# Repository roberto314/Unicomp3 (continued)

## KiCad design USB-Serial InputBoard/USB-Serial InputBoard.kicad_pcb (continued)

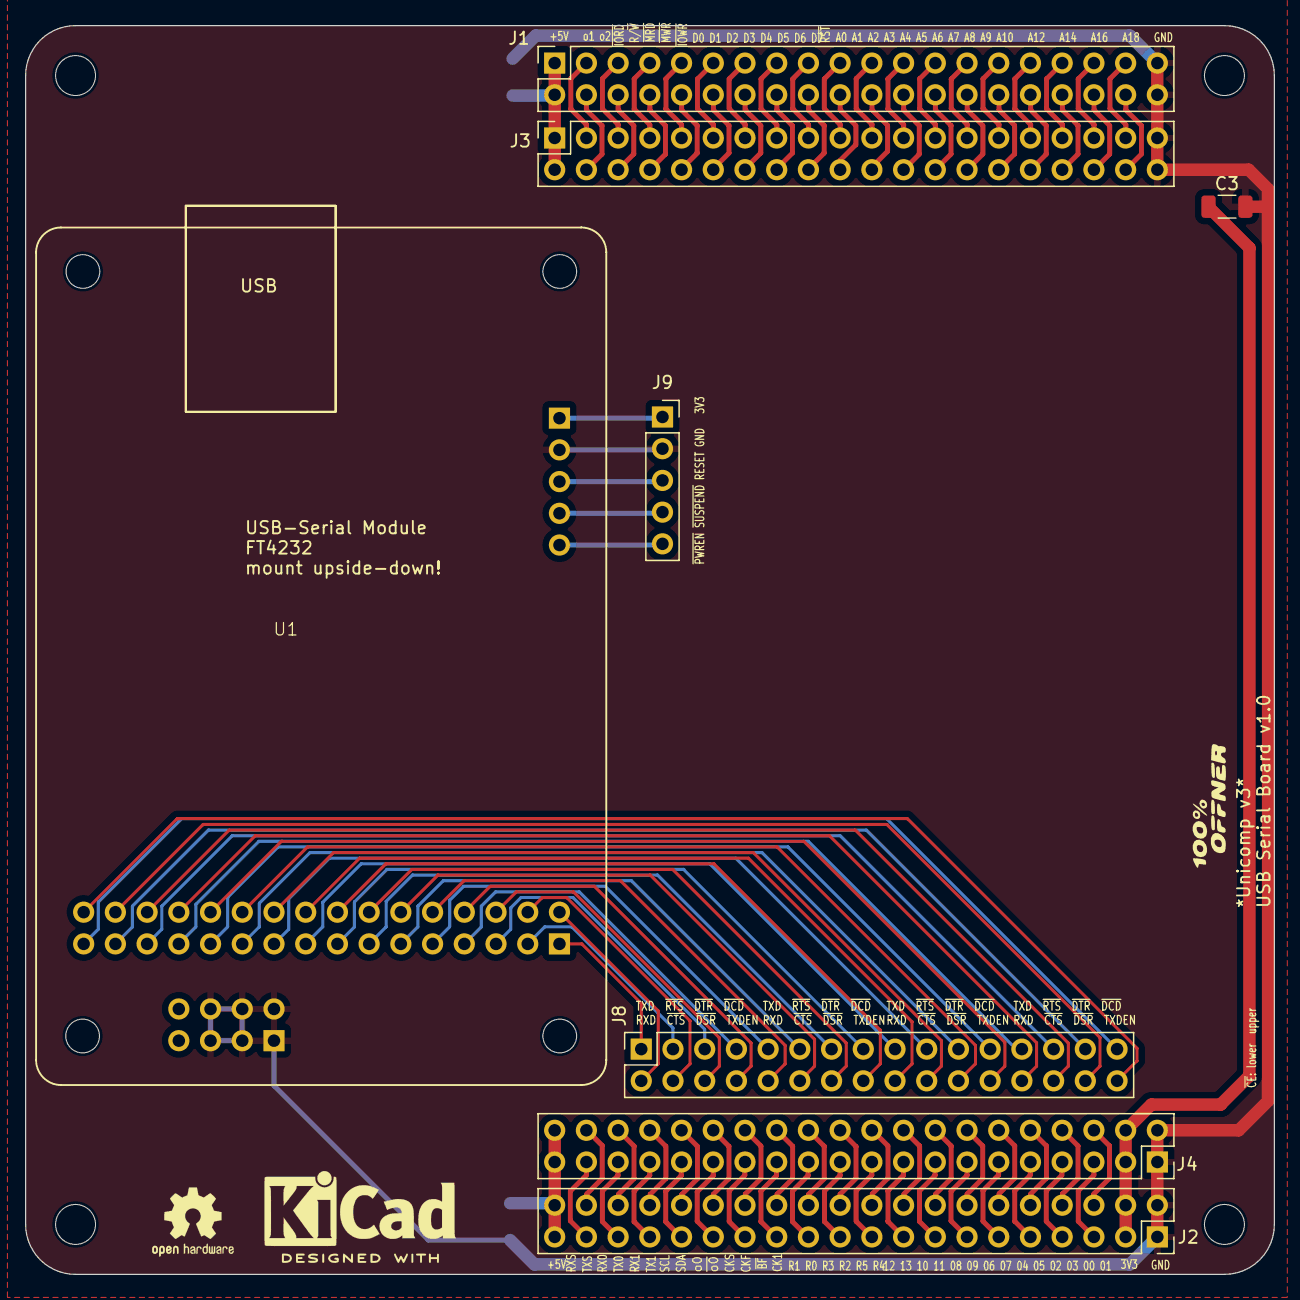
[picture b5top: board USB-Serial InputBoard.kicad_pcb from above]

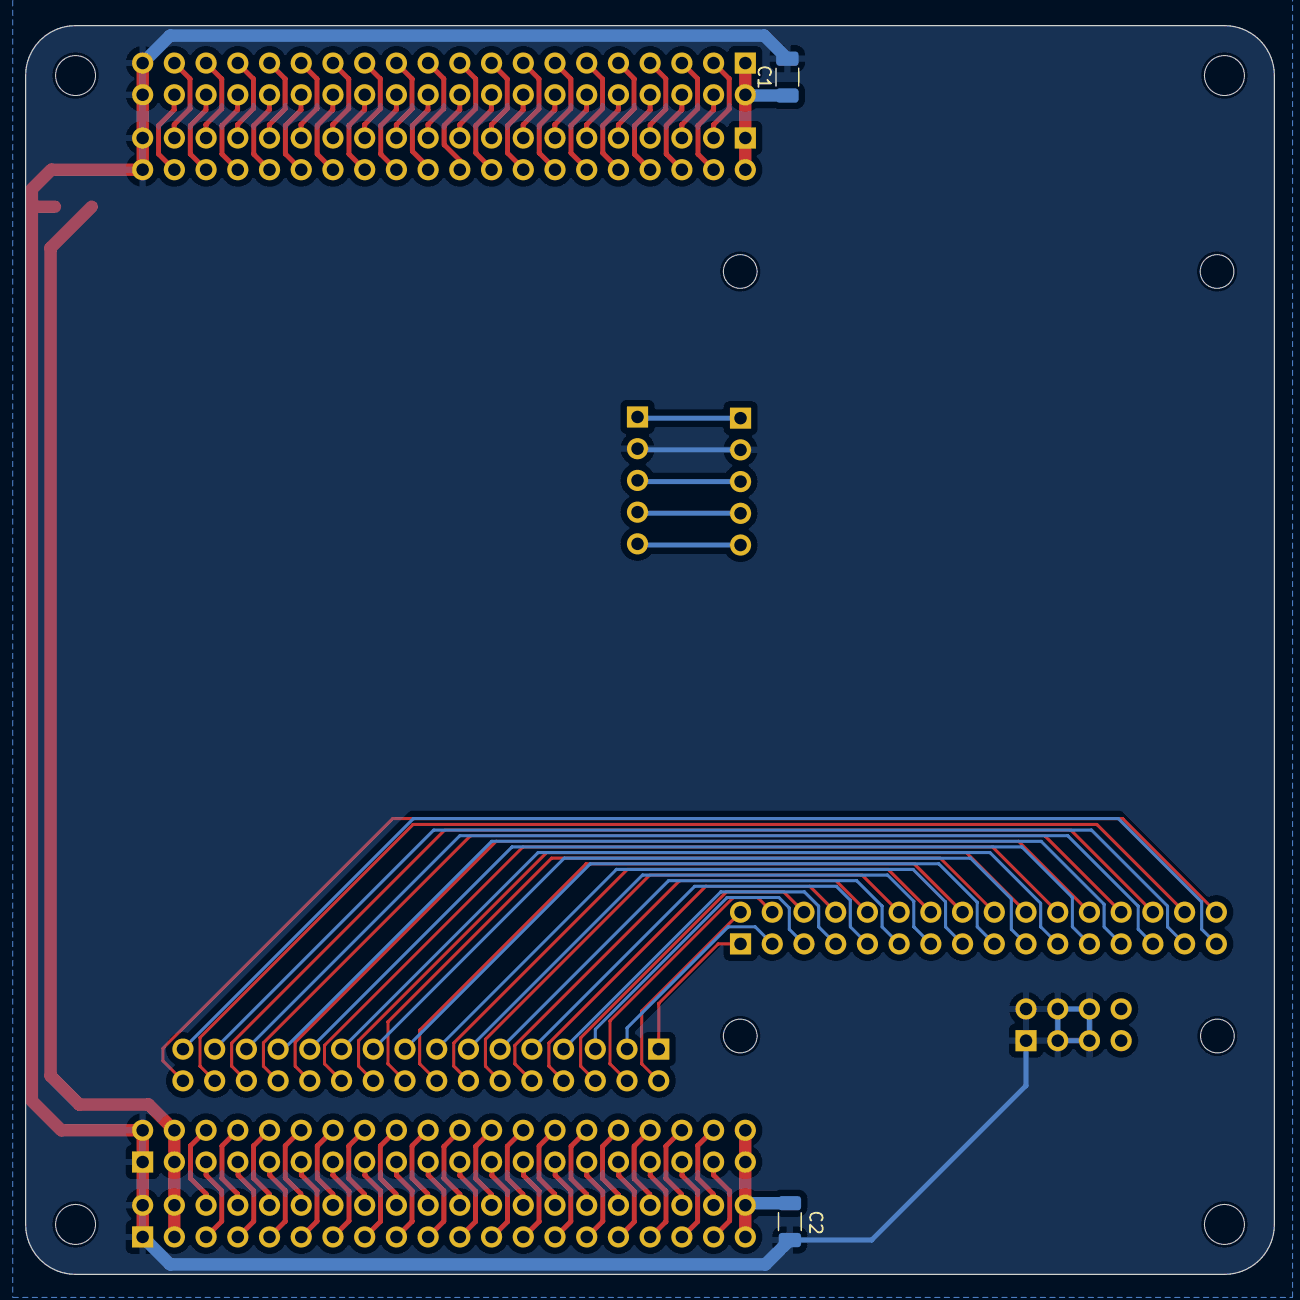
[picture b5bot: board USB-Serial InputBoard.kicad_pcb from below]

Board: 2 copper layers, 100.0 x 100.0 mm, 16 parts (2 on the bottom side), 110 nets.
